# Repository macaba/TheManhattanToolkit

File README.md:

# The Manhattan Toolkit

Electronic circuit prototyping system for reliable rapid prototyping.

- Use double sided tape to stick down SMT breakout boards onto a base board.
- Use hookup wire or bare tinned copper wire to make connections.
- Mount through-hole components directly, sometimes using islands as a convenient landing pad.
- Use pluggable terminal blocks to make external connections.
- Label your boards to ensure you don't forget what they are in future!

## Accessories

[3M 9084 9mm wide double sided tape](https://ie.rs-online.com/web/p/double-sided-tapes/5034632)  
[0.5mm diameter tinned copper wire](https://cpc.farnell.com/unbranded/tcw25-250g/tinned-copper-wire-25swg/dp/CB00044)  
[0.71mm teflon tubing](https://cpc.farnell.com/pro-elec/pelb0430/ptfe-teflon-tubing-0-71mm-clear/dp/CB22101)  
[0.19mm polyurethane coated pencil wire](https://cpc.farnell.com/pro-power/rrw-v-105-pk-4/wire-0-19mm-purple-pk-4/dp/PC01666)  
[18mm M3 female hex threaded black nylon standoff](https://www.amazon.co.uk/gp/product/B07FS9B4Q1)  
[3W 3.5mm pluggable terminal block socket](https://cpc.farnell.com/camdenboss/ctbp93hd-3/term-block-header-8a-3p-3-5mm/dp/CN20920)  
[3W 3.5mm pluggable terminal block](https://cpc.farnell.com/camdenboss/ctbp92hd-3/terminal-block-pluggable-8a-3p/dp/CN20880)

## Generic boards

The generic boards are breakout boards for a variety of standard component packages.

## Application specific boards

The application specific boards are boards that: 1. add supporting components to a specific part, or 2. perform specific useful functionality.

Example boards include ADC-A-v1 which uses the high precision AD4630-24 ADC, and LPF-A-v1 which provides a DC precise low pass filter function.

## Collection to scale

(0.2mm per pixel)

## Example prototypes

## Base-A-v1

4 layer base board in 160x100mm eurocard form factor. The grid is connected to 0V. There are 4 possible power planes which have corresponding connectors; A/B/C/D. There are 8 signal rails which have corresponding connectors; F1/F2/F3/F4/R1/R2/R3/R4 (4 front/4 rear, split into 2 top/2 bottom) typically used for input/output signals. The M3 holes are for generic mounting. The unplated holes are for Schroff front panel brackets to allow prototypes to be easy mounted in a eurocard chassis with an attractive front panel. The narrow empty region at top/bottom are keepout areas to allow the card to slide on chassis rails.

Connectors along the right edge are 3.5mm pitch pluggable terminal blocks. Socket part number: CTBP93HD/3. Plug part number: CTBP92HD/3. The footprint will be compatible with many manufacturers.

The parts for mounting to a eurocard front panel are [shown here.](images/Schroff-parts.png)

## Sizes

Base-A-v1 grid unit = 5mm  
Breakout PCB corner radius = 0.75mm (new) 1.0mm (old)  
Breakout pad = 2mm square with 0.25mm corner radius  
Breakout pad centre to edge distance = 1.5mm (hence 0.5mm clearance between edge of pad and edge of PCB)

(Breakout) - (Width x Height)  
SOIC8-A-v1 - 20mm x 10.5mm  
1.27mm-A-v1 - 20mm x 20.5mm  
1.27mm-B-v1 - 25mm x 35.5mm  
0.65mm-A-v1 - 20mm x 20.5mm  
0.65mm-B-v1 - 25mm x 35.5mm  
QFN20-A-v1 - 15mm x 20.5mm
MSOP8-A-v1 - 20mm x 10.5mm  
Islands4x4-A-v1 - 11.5mm x 11.5mm  
SOT23-A-v1 - 10mm x 8mm  
0603-A-v1 - 10mm x 10.5mm  
0805-A-v1 - 10mm x 10.5mm  
1206-A-v1 - 10mm x 10.5mm  
1210-A-v1 - 10mm x 10.5mm

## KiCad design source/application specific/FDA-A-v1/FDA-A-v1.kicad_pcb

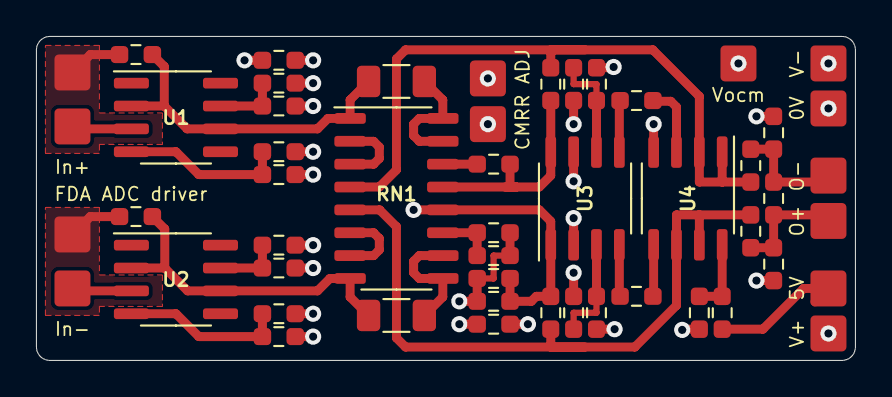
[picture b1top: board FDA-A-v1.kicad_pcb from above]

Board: 4 copper layers, 45.5 x 18.0 mm, 52 parts (0 on the bottom side), 36 nets.

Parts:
C1, C2, C3, C4, C5, C6, C9, C13: 1u; R_0603_1608Metric_Pad0.98x0.95mm_HandSolder
C7, C8: 10p; R_0603_1608Metric_Pad0.98x0.95mm_HandSolder
C10, C11: 4.7n; R_0603_1608Metric_Pad0.98x0.95mm_HandSolder
C12: 1n; R_0603_1608Metric_Pad0.98x0.95mm_HandSolder
J1, J2, J3, J4, J5, J6, J7, J8, J9, J10, J11, J12, J13: Conn_01x01_Pin; Manhattan-2mm
R1, R2, R14: 10k; R_0603_1608Metric_Pad0.98x0.95mm_HandSolder
R3, R4, R5, R6, R12, R13, R17: 2.2; R_0603_1608Metric_Pad0.98x0.95mm_HandSolder
R7, R8, R9, R10, R18, R19: 10; R_0603_1608Metric_Pad0.98x0.95mm_HandSolder
R11: TBD; R_0603_1608Metric_Pad0.98x0.95mm_HandSolder
R15, R16: 1k; R_0603_1608Metric_Pad0.98x0.95mm_HandSolder
R20, R21: 0; R_1206_3216Metric_Pad1.30x1.75mm_HandSolder
RN1: 2k; SO-16_3.9x9.9mm_P1.27mm
U1, U2: OPA140; SOIC-8_3.9x4.9mm_P1.27mm
U3: THP210; SO-8_3.9x4.9mm_P1.27mm
U4: TLV3542; SO-8_3.9x4.9mm_P1.27mm

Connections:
+5.5: J8.1, R17.1
+19: J5.1, R3.1, R6.1, R12.1, R14.2
-15.5: J6.1, R4.1, R5.1, R13.1
/Guard+: J1.1, R1.1
/Guard-: J2.1, R2.1
/IN+: J3.1, U1.3 (+)
/IN-: J4.1, U2.3 (+)
/OUT+: C11.2, C12.2, J13.1, R19.2
/OUT-: C10.1, C12.1, J12.1, R18.2
/VOCM: C13.1, J9.1, U3.2 (VOCM)
GND: C1.1, C2.1, C3.1, C4.1, C5.1, C6.1, C9.1, C10.2, C11.1, C13.2, J7.1, U4.4 (V-)
unnamed: C6.2, R13.2, U3.6 (V-)
unnamed: C8.1, J10.1, R10.1, R11.2, RN1.12 (R5.2), U3.1 (-)
unnamed: J11.1, R7.1, R8.1, R10.2, R11.1
unnamed: R15.1, U3.5 (-)
unnamed: R16.1, U3.4 (+)
unnamed: R1.2, R20.1, RN1.1 (R1.1), U1.2 (-), U1.6
unnamed: R20.2, RN1.15 (R2.2), RN1.16 (R1.2)
unnamed: RN1.2 (R2.1), RN1.3 (R3.1)
unnamed: R9.1, RN1.14 (R3.2)
unnamed: C7.2, R18.1, RN1.4 (R4.1), U4.1, U4.2 (-)
unnamed: C7.1, R9.2, RN1.13 (R4.2), U3.8 (+)
unnamed: C8.2, R19.1, RN1.5 (R5.1), U4.6 (-), U4.7
unnamed: RN1.6 (R6.1), RN1.7 (R7.1)
unnamed: R7.2, R8.2, RN1.11 (R6.2)
unnamed: R21.2, RN1.9 (R8.2), RN1.10 (R7.2)
unnamed: R2.2, R21.1, RN1.8 (R8.1), U2.2 (-), U2.6
unnamed: C1.2, R3.2, U1.7 (V+)
unnamed: C2.2, R4.2, U1.4 (V-)
unnamed: C4.2, R6.2, U2.7 (V+)
unnamed: C3.2, R5.2, U2.4 (V-)
unnamed: C5.2, R12.2, U3.3 (V+)
unnamed: R14.1, U3.7 (~SHDN)
unnamed: R15.2, U4.3 (+)
unnamed: R16.2, U4.5 (+)
unnamed: C9.2, R17.2, U4.8 (V+)

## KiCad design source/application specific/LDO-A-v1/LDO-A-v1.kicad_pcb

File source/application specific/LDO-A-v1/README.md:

# LDO-A-v1

Contributed by [NNNILabs](https://github.com/NNNILabs).

TL1963 with supporting components.

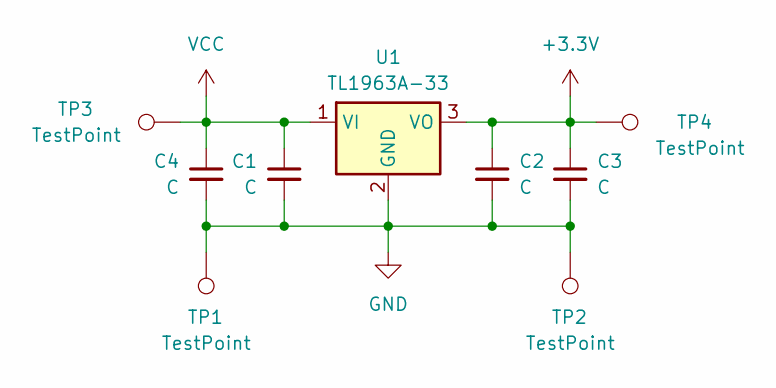
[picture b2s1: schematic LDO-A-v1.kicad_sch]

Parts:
C1, C2, C3, C4: C; C_1206_3216Metric
TP1, TP2, TP3, TP4: TestPoint; TestPoint_Pad_2.0x2.0mm
U1: TL1963A-33; SOT-223-3_TabPin2

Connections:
+3.3V: C2.1, C3.1, TP4.1, U1.3 (VO)
GND: C1.2, C2.2, C3.2, C4.2, TP1.1, TP2.1, U1.2 (GND)
VCC: C1.1, C4.1, TP3.1, U1.1 (VI)

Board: 2 copper layers, 9 parts (0 on the bottom side), 3 nets, no tracks yet.

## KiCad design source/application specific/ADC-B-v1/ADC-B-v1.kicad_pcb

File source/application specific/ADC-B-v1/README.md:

# ADC-B-v1

Contributed by [NNNILabs](https://github.com/NNNILabs).

AD7276 with supporting components and OPA354 input buffer.

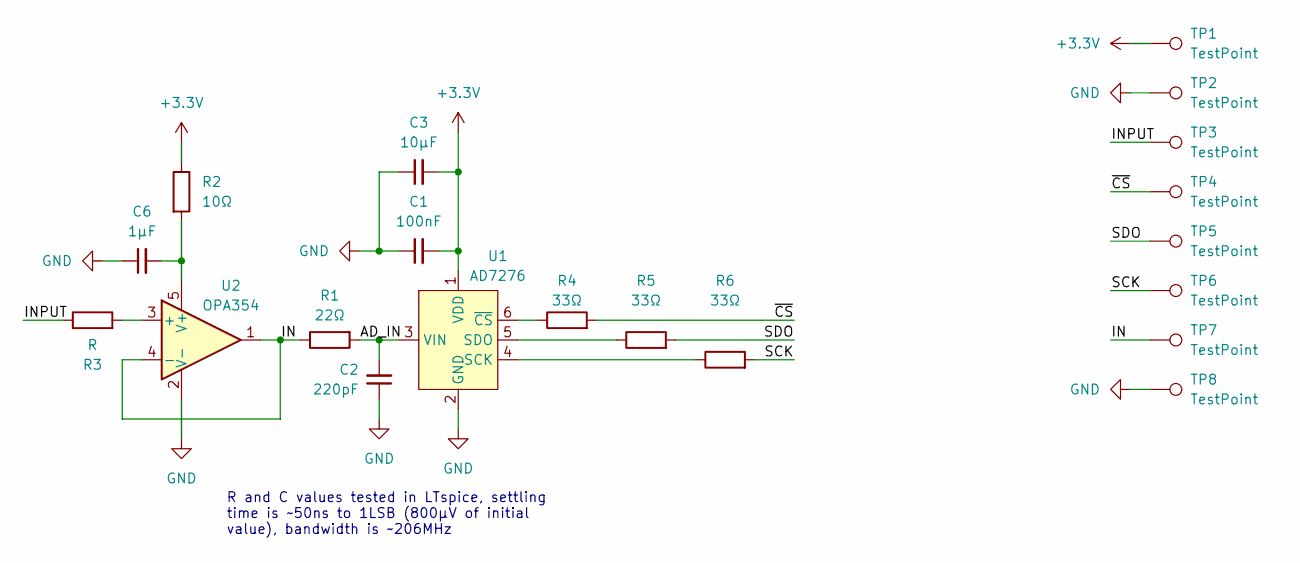
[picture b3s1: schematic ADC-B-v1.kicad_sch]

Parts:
C1: 100nF; C_0603_1608Metric_Pad1.08x0.95mm_HandSolder
C2: 220pF; C_0603_1608Metric_Pad1.08x0.95mm_HandSolder
C3: 10μF; C_1206_3216Metric_Pad1.33x1.80mm_HandSolder
C6: 1μF; C_0603_1608Metric_Pad1.08x0.95mm_HandSolder
R1: 22Ω; R_0603_1608Metric_Pad0.98x0.95mm_HandSolder
R2: 10Ω; R_0603_1608Metric_Pad0.98x0.95mm_HandSolder
R3: R; R_0603_1608Metric_Pad0.98x0.95mm_HandSolder
R4, R5, R6: 33Ω; R_0603_1608Metric_Pad0.98x0.95mm_HandSolder
TP1, TP2, TP3, TP4, TP5, TP6, TP7, TP8: TestPoint; TestPoint_Pad_2.0x2.0mm
U1: AD7276; TSOT-23-6
U2: OPA354; SOT-23-5

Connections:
+3.3V: C1.2, C3.2, R2.1, TP1.1, U1.1 (VDD)
/AD_IN: C2.2, R1.2, U1.3 (VIN)
/IN: R1.1, TP7.1, U2.1, U2.4 (-)
/INPUT: R3.1, TP3.1
/SCK: R6.2, TP6.1
/SDO: R5.2, TP5.1
/~CS: R4.2, TP4.1
GND: C1.1, C2.1, C3.1, C6.1, TP2.1, TP8.1, U1.2 (GND), U2.2 (V-)
unnamed: R6.1, U1.4 (SCK)
unnamed: R5.1, U1.5 (SDO)
unnamed: R4.1, U1.6 (~CS)
unnamed: R3.2, U2.3 (+)
unnamed: C6.2, R2.2, U2.5 (V+)

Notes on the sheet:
R and C values tested in LTspice, settling time is ~50ns to 1LSB (800μV of initial value), bandwidth is ~206MHz

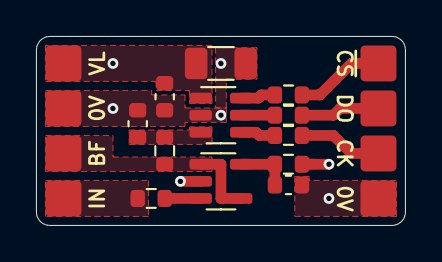
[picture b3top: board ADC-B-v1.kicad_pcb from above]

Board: 4 copper layers, 20.5 x 10.5 mm, 20 parts (0 on the bottom side), 13 nets.

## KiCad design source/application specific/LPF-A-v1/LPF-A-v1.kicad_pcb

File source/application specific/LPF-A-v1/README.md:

# LPF-A-v1

DC precise low pass filter for precision DC applications.

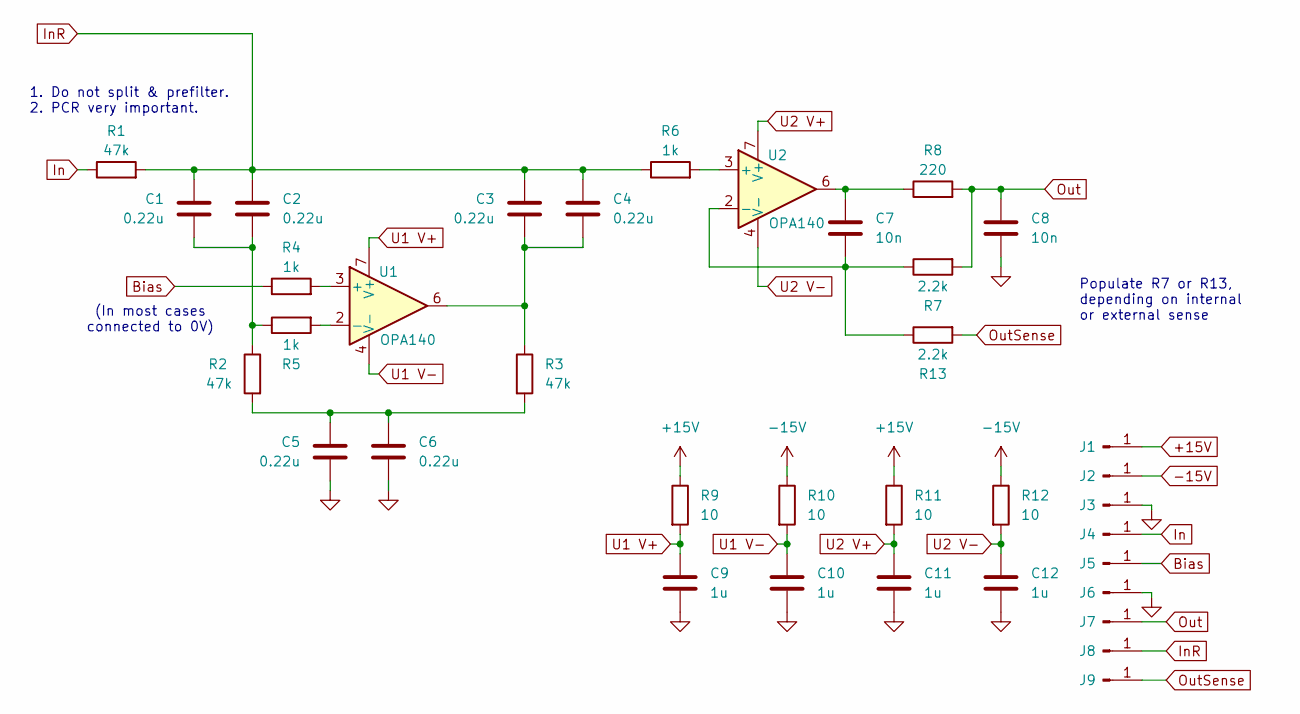
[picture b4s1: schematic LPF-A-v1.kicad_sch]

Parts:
C1, C2, C3, C4, C5, C6: 0.22u; C_1812_4532Metric_Pad1.57x3.40mm_HandSolder
C7, C8: 10n; R_0805_2012Metric_Pad1.20x1.40mm_HandSolder
C9, C10, C11, C12: 1u; R_0603_1608Metric_Pad0.98x0.95mm_HandSolder
J1, J2, J3, J4, J5, J6, J7, J8, J9: Conn_01x01_Pin; Manhattan-2mm
R1, R2, R3: 47k; R_0805_2012Metric_Pad1.20x1.40mm_HandSolder
R4, R5, R6: 1k; R_0603_1608Metric_Pad0.98x0.95mm_HandSolder
R7, R13: 2.2k; R_0603_1608Metric_Pad0.98x0.95mm_HandSolder
R8: 220; R_0603_1608Metric_Pad0.98x0.95mm_HandSolder
R9, R10, R11, R12: 10; R_0603_1608Metric_Pad0.98x0.95mm_HandSolder
U1, U2: OPA140; SOIC-8_3.9x4.9mm_P1.27mm

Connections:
+15V: J1.1, R9.1, R11.1
-15V: J2.1, R10.1, R12.1
Bias: J5.1, R4.1
GND: C5.2, C6.2, C8.2, C9.2, C10.2, C11.2, C12.2, J3.1, J6.1
In: J4.1, R1.1
InR: C1.1, C2.1, C3.1, C4.1, J8.1, R1.2, R6.1
unnamed: C1.2, C2.2, R2.1, R5.1
unnamed: C3.2, C4.2, R3.1, U1.6
unnamed: C5.1, C6.1, R2.2, R3.2
unnamed: C7.1, R8.1, U2.6
unnamed: R4.2, U1.3 (+)
unnamed: R5.2, U1.2 (-)
unnamed: R6.2, U2.3 (+)
Out: C8.1, J7.1, R7.2, R8.2
OutSense: J9.1, R13.2
U1 V+: C9.1, R9.2, U1.7 (V+)
U1 V-: C10.1, R10.2, U1.4 (V-)
U2 V+: C11.1, R11.2, U2.7 (V+)
U2 V-: C12.1, R12.2, U2.4 (V-)

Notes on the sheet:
(In most cases connected to 0V)
Populate R7 or R13, depending on internal or external sense
1. Do not split & prefilter. 2. PCR very important.

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
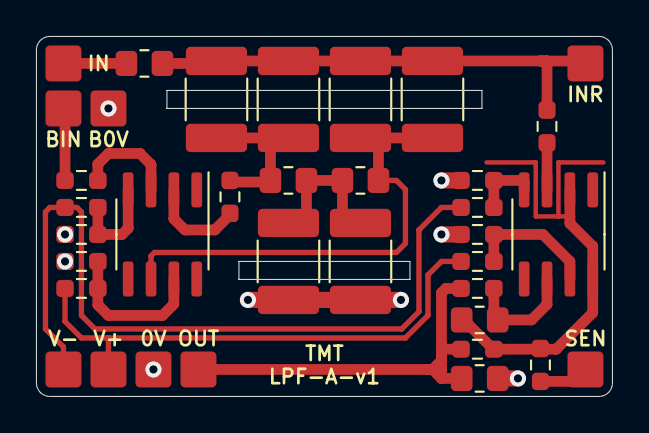
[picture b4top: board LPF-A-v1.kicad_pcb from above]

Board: 6 copper layers, 32.0 x 20.0 mm, 36 parts (0 on the bottom side), 20 nets.

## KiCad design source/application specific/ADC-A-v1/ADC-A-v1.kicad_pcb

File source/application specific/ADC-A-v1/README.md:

# ADC-A-v1

AD4630-24 ADC with supporting components.

## Components

Input R - RNCF0603DTE10R0 (10 ohm)  
Input CM C - CGA3E1C0G2A472J080AC (4.7nF)  
Input DM C - DNP

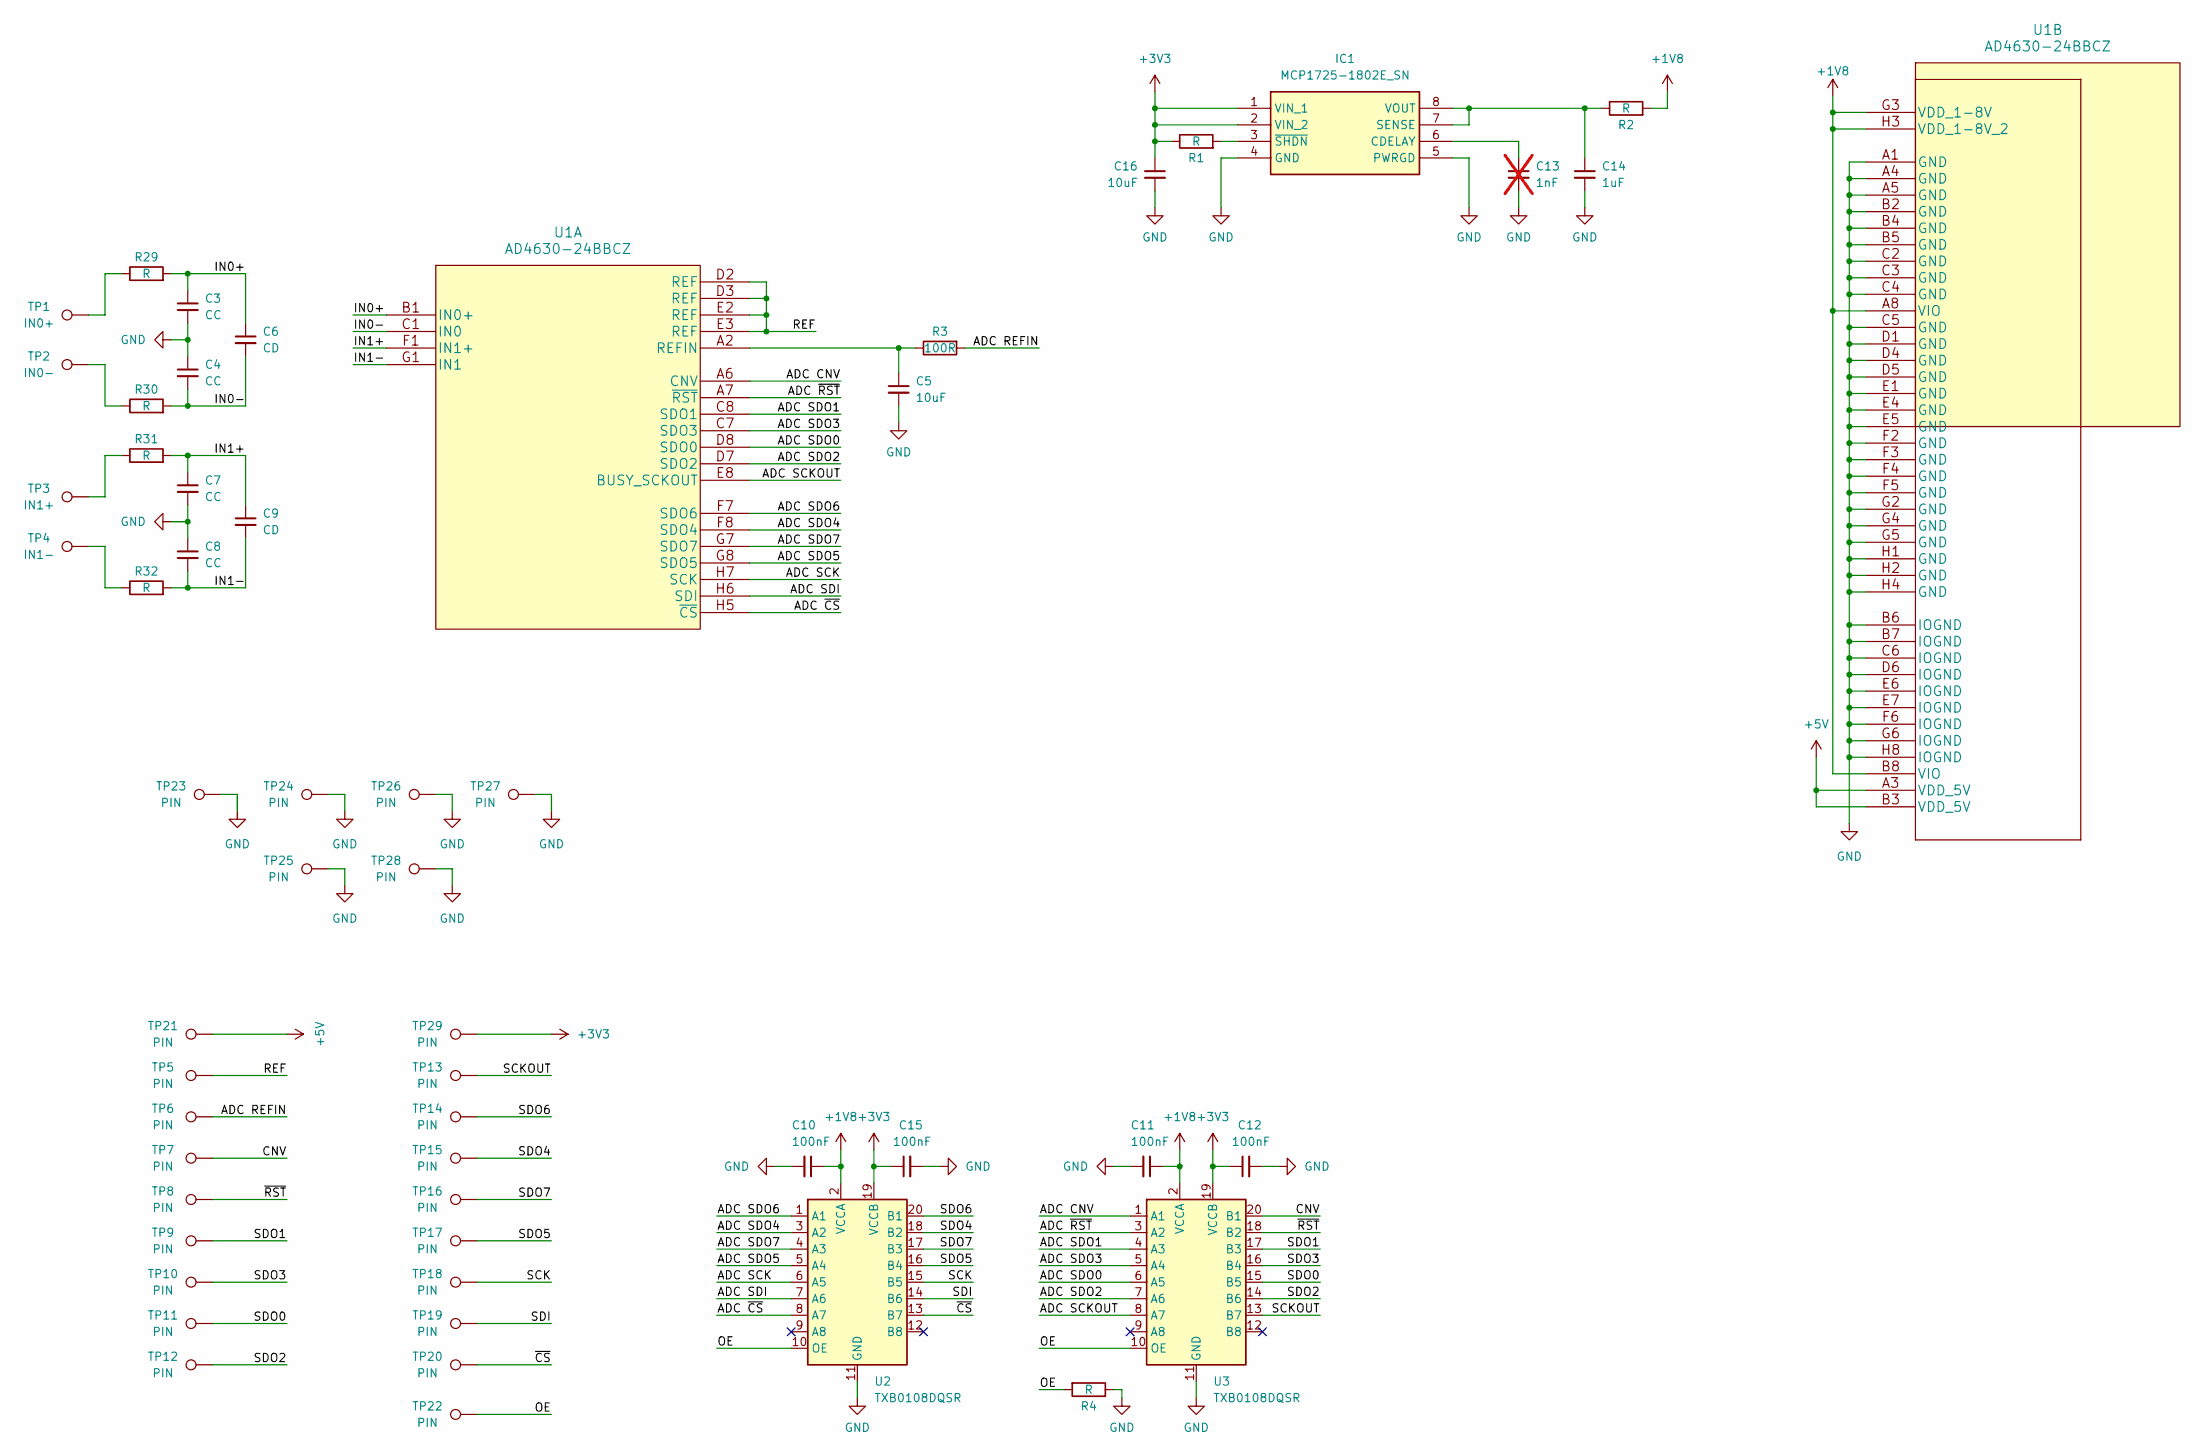
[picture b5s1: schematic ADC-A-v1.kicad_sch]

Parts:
C3, C4, C7, C8: CC; R_0603_1608Metric_Pad0.98x0.95mm_HandSolder
C5: 10uF; C_1812_4532Metric_Pad1.57x3.40mm_HandSolder
C6, C9: CD; R_0603_1608Metric_Pad0.98x0.95mm_HandSolder
C10, C11, C12, C15: 100nF; R_0603_1608Metric_Pad0.98x0.95mm_HandSolder
C13: 1nF; R_0603_1608Metric_Pad0.98x0.95mm_HandSolder; not fitted
C14: 1uF; R_0603_1608Metric_Pad0.98x0.95mm_HandSolder
C16: 10uF; R_1206_3216Metric_Pad1.30x1.75mm_HandSolder
IC1: MCP1725-1802E_SN; SOIC127P600X175-8N; Manufacturer_Part_Number MCP1725-1802E/SN; Mouser Part Number 579-MCP1725-1802E/SN
R1, R2, R4, R29, R30, R31, R32: R; R_0603_1608Metric_Pad0.98x0.95mm_HandSolder
R3: 100R; R_0603_1608Metric_Pad0.98x0.95mm_HandSolder
TP1: IN0+; TestPoint_Pad_2.0x2.0mm
TP2: IN0-; TestPoint_Pad_2.0x2.0mm
TP3: IN1+; TestPoint_Pad_2.0x2.0mm
TP4: IN1-; TestPoint_Pad_2.0x2.0mm
TP5, TP6, TP7, TP8, TP9, TP10, TP11, TP12, TP13, TP14, TP15, TP16, TP17, TP18, TP19, TP20, TP21, TP22, TP23, TP24, TP25, TP26, TP27, TP28, TP29: PIN; TestPoint_Pad_2.0x2.0mm
U1: AD4630-24BBCZ
U2, U3: TXB0108DQSR; SOP65P640X120-20N

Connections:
+1V8: C10.1, C11.1, R2.2, U1.A8 (VIO), U1.B8 (VIO), U1.G3 (VDD_1-8V), U1.H3 (VDD_1-8V_2), U2.2 (VCCA), U3.2 (VCCA)
+3V3: C12.1, C15.1, C16.1, IC1.1 (VIN_1), IC1.2 (VIN_2), R1.1, TP29.1, U2.19 (VCCB), U3.19 (VCCB)
+5V: TP21.1, U1.A3 (VDD_5V), U1.B3 (VDD_5V)
/ADC CNV: U1.A6 (CNV), U3.1 (A1)
/ADC REFIN: R3.2, TP6.1
/ADC SCK: U1.H7 (SCK), U2.6 (A5)
/ADC SCKOUT: U1.E8 (BUSY_SCKOUT), U3.8 (A7)
/ADC SDI: U1.H6 (SDI), U2.7 (A6)
/ADC SDO0: U1.D8 (SDO0), U3.6 (A5)
/ADC SDO1: U1.C8 (SDO1), U3.4 (A3)
/ADC SDO2: U1.D7 (SDO2), U3.7 (A6)
/ADC SDO3: U1.C7 (SDO3), U3.5 (A4)
/ADC SDO4: U1.F8 (SDO4), U2.3 (A2)
/ADC SDO5: U1.G8 (SDO5), U2.5 (A4)
/ADC SDO6: U1.F7 (SDO6), U2.1 (A1)
/ADC SDO7: U1.G7 (SDO7), U2.4 (A3)
/ADC ~CS: U1.H5 (~CS), U2.8 (A7)
/ADC ~RST: U1.A7 (~RST), U3.3 (A2)
/CNV: TP7.1, U3.20 (B1)
/IN0+: C3.1, C6.1, R29.2, U1.B1 (IN0+)
/IN0-: C4.2, C6.2, R30.2, U1.C1 (IN0)
/IN1+: C7.1, C9.1, R31.2, U1.F1 (IN1+)
/IN1-: C8.2, C9.2, R32.2, U1.G1 (IN1)
/OE: R4.2, TP22.1, U2.10 (OE), U3.10 (OE)
/REF: TP5.1, U1.D2 (REF), U1.D3 (REF), U1.E2 (REF), U1.E3 (REF)
/SCK: TP18.1, U2.15 (B5)
/SCKOUT: TP13.1, U3.13 (B7)
/SDI: TP19.1, U2.14 (B6)
/SDO0: TP11.1, U3.15 (B5)
/SDO1: TP9.1, U3.17 (B3)
/SDO2: TP12.1, U3.14 (B6)
/SDO3: TP10.1, U3.16 (B4)
/SDO4: TP15.1, U2.18 (B2)
/SDO5: TP17.1, U2.16 (B4)
/SDO6: TP14.1, U2.20 (B1)
/SDO7: TP16.1, U2.17 (B3)
/~CS: TP20.1, U2.13 (B7)
/~RST: TP8.1, U3.18 (B2)
GND: C3.2, C4.1, C5.2, C7.2, C8.1, C10.2, C11.2, C12.2, C13.2, C14.2, C15.2, C16.2, IC1.4 (GND), IC1.5 (PWRGD), R4.1, TP23.1, TP24.1, TP25.1, TP26.1, TP27.1, TP28.1, U1.A1 (GND), U1.A4 (GND), U1.A5 (GND), U1.B2 (GND), U1.B4 (GND), U1.B5 (GND), U1.B6 (IOGND), U1.B7 (IOGND), U1.C2 (GND), U1.C3 (GND), U1.C4 (GND), U1.C5 (GND), U1.C6 (IOGND), U1.D1 (GND), U1.D4 (GND), U1.D5 (GND), U1.D6 (IOGND), U1.E1 (GND), U1.E4 (GND), U1.E5 (GND), U1.E6 (IOGND), U1.E7 (IOGND), U1.F2 (GND), U1.F3 (GND), U1.F4 (GND), U1.F5 (GND), U1.F6 (IOGND), U1.G2 (GND), U1.G4 (GND), U1.G5 (GND), U1.G6 (IOGND), U1.H1 (GND), U1.H2 (GND), U1.H4 (GND), U1.H8 (IOGND), U2.11 (GND), U3.11 (GND)
unnamed: C13.1, IC1.6 (CDELAY)
unnamed: C14.1, IC1.7 (SENSE), IC1.8 (VOUT), R2.1
unnamed: IC1.3 (~SHDN), R1.2
unnamed: R29.1, TP1.1
unnamed: R30.1, TP2.1
unnamed: R31.1, TP3.1
unnamed: R32.1, TP4.1
unnamed: C5.1, R3.1, U1.A2 (REFIN)

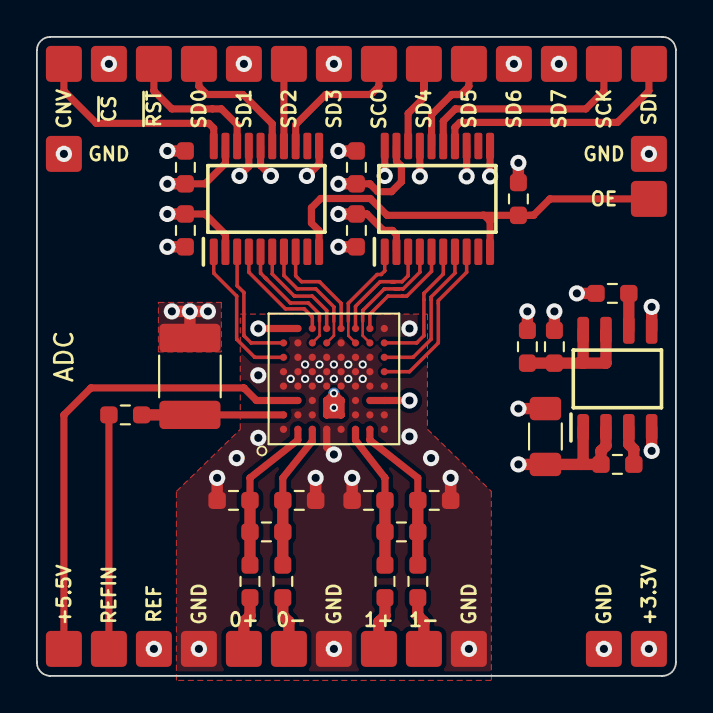
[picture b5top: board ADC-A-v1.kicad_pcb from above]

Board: 6 copper layers, 35.5 x 35.5 mm, 55 parts (0 on the bottom side), 47 nets.

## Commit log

2023-01-28 Base-A-v1
2023-01-28 Updated gerbers
2023-01-28 SOIC8-A-v1 images
2023-01-28 Passive breakouts
2023-01-28 Islands4x4-A-v1
2023-01-28 1.27mm-A-v1
2023-01-28 MSOP8-A-v1
2023-01-28 SOT23-A-v1
2023-06-07 Added details of Schroff parts
2023-11-02 PWM DAC
2023-11-07 Added 3 more breakouts
2023-11-07 Added QFN20-A-v1
2024-08-03 ADC-A-v1
2024-08-03 ADC-A-v1 photo
2024-08-03 Update ADC-A-v1.kicad_sch
    Fixed AD4630 schematic symbol issue
2024-08-04 LPF-A-v1
2024-08-15 Switched 0805 resistor to 1206
2024-08-17 Fixed position of silk label
2024-08-18 Added pad for external resistor input
2024-08-25 Updated output capacitors to 0805
2024-08-25 Added pad to allow for external sense
2024-08-25 Tweaked silk
2024-09-02 Tided up repo
2024-12-02 Added ADC-B-v1
2024-12-11 Updated ADC-B-v1
2024-12-11 Added LDO-A-v1
2025-03-30 FDA-A-v1 for review
